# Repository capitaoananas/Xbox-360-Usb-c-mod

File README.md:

# Xbox-360-Usb-c-mod

A litle breakout board for usb c so you dont need to hassle with the built in cable on the xbox 360 controller

## Bill of Materials (BOM)
| Part        | Quantity | Price  | Link                                                                                                                                                                                                                                                                                                                                                                                                                                                                                                                                                                                                                                                                                                                                               | Notes                                |
| ----------- | -------- | ------ | -------------------------------------------------------------------------------------------------------------------------------------------------------------------------------------------------------------------------------------------------------------------------------------------------------------------------------------------------------------------------------------------------------------------------------------------------------------------------------------------------------------------------------------------------------------------------------------------------------------------------------------------------------------------------------------------------------------------------------------------------- | ------------------------------------ |
| PCB         | 5        | $22.83 | [jlcpcb](https://jlcpcb.com/)                                                                                                                                                                                                                                                                                                                                                                                                                                                                                                                                                                                                                                                                                                                      |                                      |
| USB-C       | 5        | $12.34 | [lcsc](https://lcsc.com)                                                                                                                                                                                                                                                                                                                                                                                                                                                                                                                                                                                                                                                                                                                           | only place that has this exact usb c |
| Pin headers | 5        | $2.32  | [aliexpress](https://pt.aliexpress.com/item/1005004350855974.html?spm=a2g0o.detail.pcDetailTopMoreOtherSeller.1.2fc92GyW2GyWVd&gps-id=pcDetailTopMoreOtherSeller&scm=1007.40050.354490.0&scm_id=1007.40050.354490.0&scm-url=1007.40050.354490.0&pvid=be78f20b-22a2-4f41-bc30-688b49218bc8&_t=gps-id:pcDetailTopMoreOtherSeller,scm-url:1007.40050.354490.0,pvid:be78f20b-22a2-4f41-bc30-688b49218bc8,tpp_buckets:668%232846%238112%231997&pdp_ext_f=%7B%22order%22%3A%2277%22%2C%22eval%22%3A%221%22%2C%22sceneId%22%3A%2230050%22%7D&pdp_npi=4%40dis%21EUR%211.96%211.96%21%21%212.24%212.24%21%40210390c917531857012155516e08b5%2112000028860591754%21rec%21PT%216372042523%21XZ&utparam-url=scene%3ApcDetailTopMoreOtherSeller%7Cquery_from%3A) |                                      |

**Total: $37.49**

# Overview

Schematic             |  PCB
:-------------------------:|:-------------------------:
  |  

---

3D top             |  3D bottom
:-------------------------:|:-------------------------:
  |  

---

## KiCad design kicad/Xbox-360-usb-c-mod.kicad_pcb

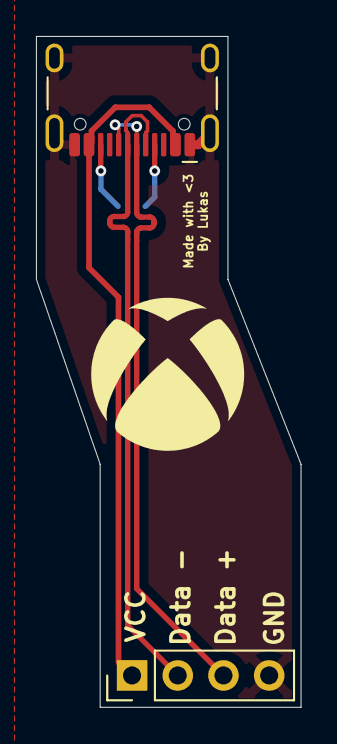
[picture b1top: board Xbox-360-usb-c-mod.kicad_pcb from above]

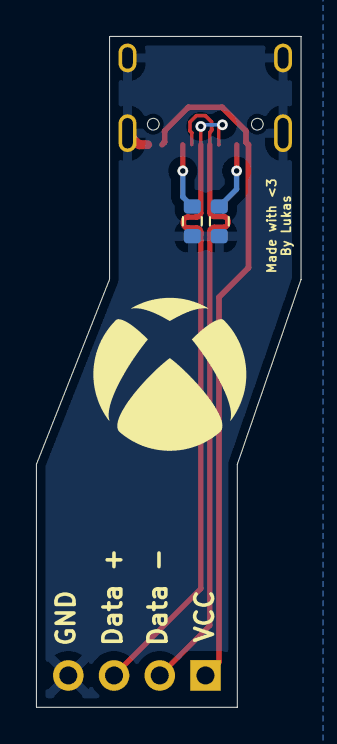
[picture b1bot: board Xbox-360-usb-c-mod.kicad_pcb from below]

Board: 2 copper layers, 14.7 x 37.3 mm, 4 parts (2 on the bottom side), 6 nets.

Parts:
Header_PIN1: Conn_01x04_Pin; PinHeader_1x04_P2.54mm_Vertical
R1, R2: R_Small; R_0603_1608Metric
USB_C1: USB_C_Receptacle_USB2.0_16P; USB_C_Receptacle_HCTL_HC-TYPE-C-16P-01A

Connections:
+5V: Header_PIN1.1, USB_C1.A4 (VBUS), USB_C1.A9 (VBUS), USB_C1.B4 (VBUS), USB_C1.B9 (VBUS)
/D+: Header_PIN1.3, USB_C1.A6 (D+), USB_C1.B6 (D+)
/D-: Header_PIN1.2, USB_C1.A7 (D-), USB_C1.B7 (D-)
GND: Header_PIN1.4, R1.2, R2.2, USB_C1.A1 (GND), USB_C1.A12 (GND), USB_C1.B1 (GND), USB_C1.B12 (GND), USB_C1.S1 (SHIELD)
unnamed: R1.1, USB_C1.A5 (CC1)
unnamed: R2.1, USB_C1.B5 (CC2)

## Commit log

2025-07-21 add pcb
2025-07-22 Journal and Readme
